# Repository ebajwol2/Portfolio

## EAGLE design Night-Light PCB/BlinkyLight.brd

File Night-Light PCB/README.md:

Night-Light PCB — Custom Board Design (EAGLE)
=============================================

GitHub Repo Description (Short)
-------------------------------

Custom LED night-light PCB designed in EAGLE. Includes schematic, layout, ERC/DRC verification, Gerbers, and assembled/soldered final board.

Full Description
----------------

Designed, fabricated, and assembled a simple LED night-light PCB using Autodesk EAGLE.

Features
--------

- LED + resistor + transistor simple lighting circuit
- Clean schematic and PCB layout
- ERC/DRC checks all passed
- Generated Gerber files for fabrication
- Fully soldered and tested working board

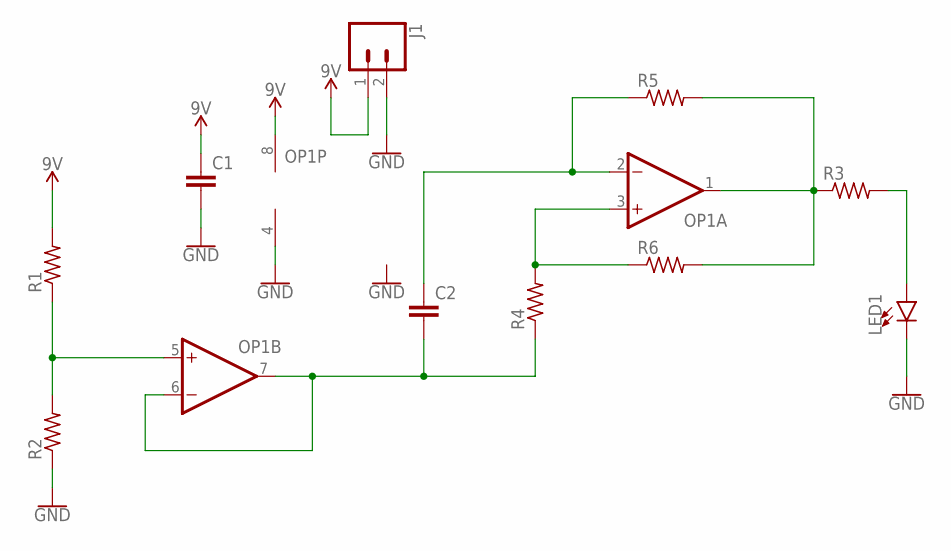
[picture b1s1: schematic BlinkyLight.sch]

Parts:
C1, C2: CAPACITOR0603; C0603
J1: CONN_02; 1X02
LED1: LED5MM; LED_5MM
OP1: OP-DUALR; SO8
R1, R2, R3, R4, R5, R6: RESISTOR0603; R0603

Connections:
9V: C1.1, J1.1, OP1.8 (V+), R1.2
GND: C1.2, J1.2, LED1.K (C), OP1.4 (V-), R2.1
unnamed: OP1.5 (+IN), R1.1, R2.2
unnamed: C2.2, OP1.6 (-IN), OP1.7 (OUT), R4.1
unnamed: OP1.3 (+IN), R4.2, R6.1
unnamed: OP1.1 (OUT), R3.1, R5.2, R6.2
unnamed: LED1.A, R3.2
unnamed: C2.1, OP1.2 (-IN), R5.1

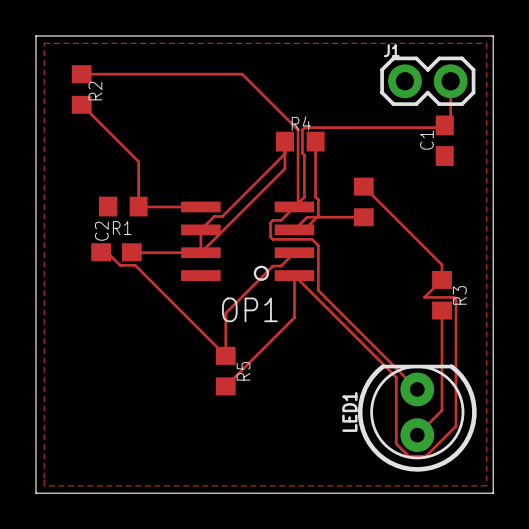
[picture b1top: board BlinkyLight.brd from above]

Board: 2 copper layers, 25.4 x 25.4 mm, 11 parts (0 on the bottom side), 8 nets.

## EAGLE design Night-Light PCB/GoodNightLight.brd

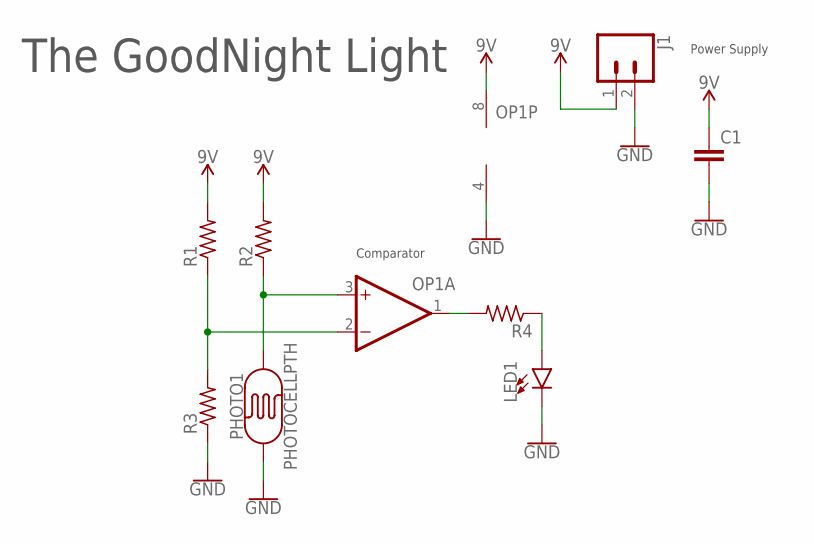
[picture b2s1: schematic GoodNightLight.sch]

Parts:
C1: CAPACITOR0603; C0603
J1: CONN_02; 1X02
LED1: LED5MM; LED_5MM
OP1: OP-DUALR; SO8
PHOTO1: PHOTOCELLPTH; PHOTOCELL
R1, R2, R3, R4: RESISTOR0603; R0603

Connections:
9V: C1.1, J1.1, OP1.8 (V+), R1.2, R2.2
GND: C1.2, J1.2, LED1.K (C), OP1.4 (V-), PHOTO1.1, R3.1
unnamed: OP1.3 (+IN), PHOTO1.2, R2.1
unnamed: OP1.1 (OUT), R4.2
unnamed: OP1.2 (-IN), R1.1, R3.2
unnamed: LED1.A, R4.1

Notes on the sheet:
The GoodNight Light
Comparator
Power Supply

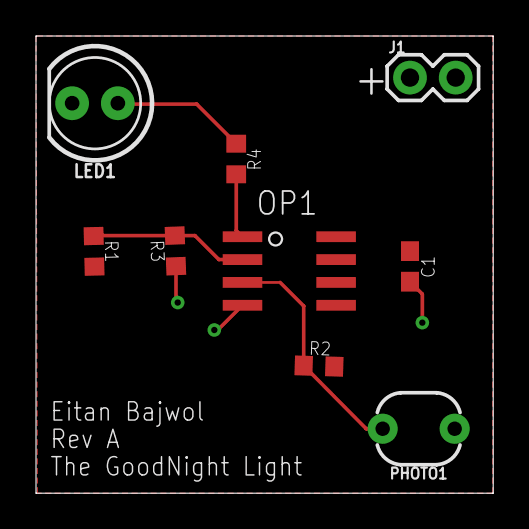
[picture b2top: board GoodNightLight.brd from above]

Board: 2 copper layers, 25.4 x 25.4 mm, 9 parts (0 on the bottom side), 6 nets.

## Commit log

2025-10-16 Update@
2025-11-17 Add FPGA Moon Lander, 16-bit CPU, RP2350 monitor, Night-Light PCB docs
